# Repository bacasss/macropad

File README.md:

NOTE: for latest images, scroll down. I think these old images still have some value to this haha

this is a 3x4 macropad, utilising 12 keys wired via matrix wiring with a rotary encoder and an oled display. the main microcontroller is a seeed studio xiao rp2040.

this is the first (well second time including the 1 x 3 example) creating a pcb and it was so fun learning, drawing and arranging the components and it took so long but i feel that its a vital skill that i'll definately need to touch on again

note: native files in cad folder

BOM:
1 Seeed XIAO RP2040
12x 1N4148 Diodes
12x MX-Style switches
1x EC11 Rotary encoders
1x 0.91 inch OLED display
12x white blank DSA keycaps
4x M3x16mm screws
4x M3x5mx4mm heatset inserts

Full mockup:

this is a full mockup of the entire design, including switches, the rotary encoder, the microcontroller, and the oled display

Schematic:

i ONLY found out there was a much neater way for my pcb schematic AFTER i finished it so apologies for the mess, but it was a new experience learning matrix wiring for efficient pin usage

PCB:

i tried to make the pcb as nice as possible, but this took so long haha
here it is in 3D:

final (apparently not) update, heres an image of the assembly with a translucent top plate:

andd heres the back without the cover:

UPDATE: added mounting holes to PCB and Caseee:

PCB with mouthing holes:

In 3D:

The back of the PCB in 3D:

Updated the case with holes to mount the PCB on:

Clearer view of said holes because image isnt that clear on showing it:

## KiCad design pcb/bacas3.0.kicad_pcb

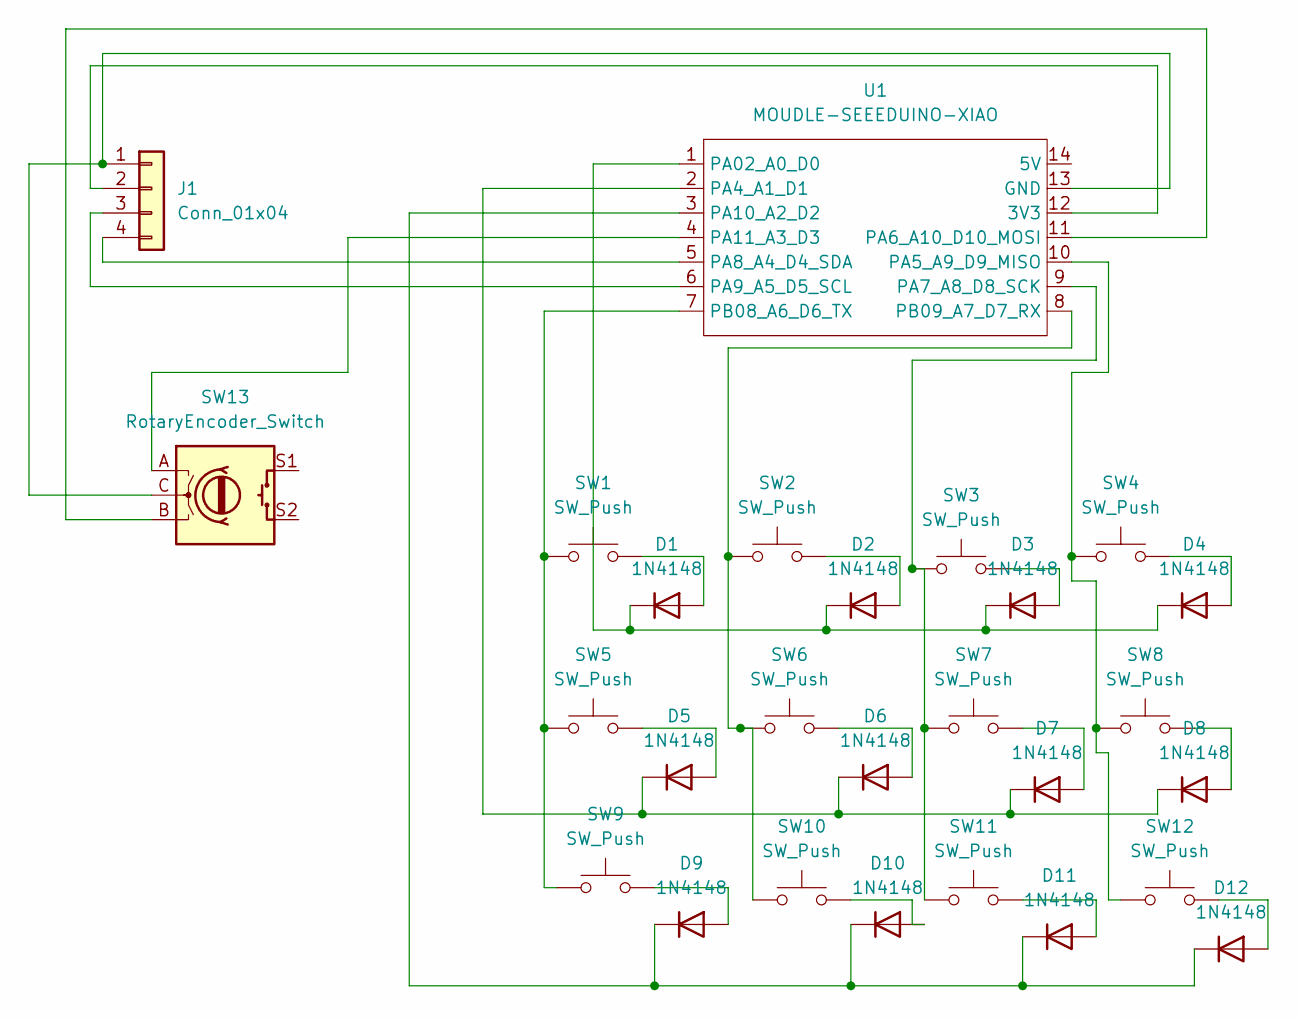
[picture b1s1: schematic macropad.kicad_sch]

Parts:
D1, D2, D3, D4, D5, D6, D7, D8, D9, D10, D11, D12: 1N4148; D_DO-35_SOD27_P7.62mm_Horizontal
J1: Conn_01x04; SSD1306-0.91-OLED-4pin-128x32 (1)
SW1, SW2, SW3, SW4, SW5, SW6, SW7, SW8, SW9, SW10, SW11, SW12: SW_Push; SW_Cherry_MX_1.00u_PCB
SW13: RotaryEncoder_Switch; RotaryEncoder_Alps_EC11E-Switch_Vertical_H20mm
U1: MOUDLE-SEEEDUINO-XIAO; XIAO-Generic-Hybrid-14P-2.54-21X17.8MM

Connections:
unnamed: D1.2 (A), SW1.2
unnamed: D1.1 (K), D2.1 (K), D3.1 (K), D4.1 (K), U1.1 (PA02_A0_D0)
unnamed: D2.2 (A), SW2.2
unnamed: D3.2 (A), SW3.2
unnamed: D4.2 (A), SW4.2
unnamed: D5.2 (A), SW5.2
unnamed: D5.1 (K), D6.1 (K), D7.1 (K), D8.1 (K), U1.2 (PA4_A1_D1)
unnamed: D6.2 (A), SW6.2
unnamed: D7.2 (A), SW7.2
unnamed: D8.2 (A), SW8.2
unnamed: D9.2 (A), SW9.2
unnamed: D10.2 (A), SW10.2
unnamed: D9.1 (K), D10.1 (K), D11.1 (K), D12.1 (K), U1.3 (PA10_A2_D2)
unnamed: D11.2 (A), SW11.2
unnamed: D12.2 (A), SW12.2
unnamed: J1.1, SW13.C, U1.13 (GND)
unnamed: J1.2, U1.12 (3V3)
unnamed: J1.3, U1.6 (PA9_A5_D5_SCL)
unnamed: J1.4, U1.5 (PA8_A4_D4_SDA)
unnamed: SW4.1, SW8.1, SW12.1, U1.10 (PA5_A9_D9_MISO)
unnamed: SW13.B, U1.11 (PA6_A10_D10_MOSI)
unnamed: SW3.1, SW7.1, SW11.1, U1.9 (PA7_A8_D8_SCK)
unnamed: SW13.A, U1.4 (PA11_A3_D3)
unnamed: SW1.1, SW5.1, SW9.1, U1.7 (PB08_A6_D6_TX)
unnamed: SW2.1, SW6.1, SW10.1, U1.8 (PB09_A7_D7_RX)

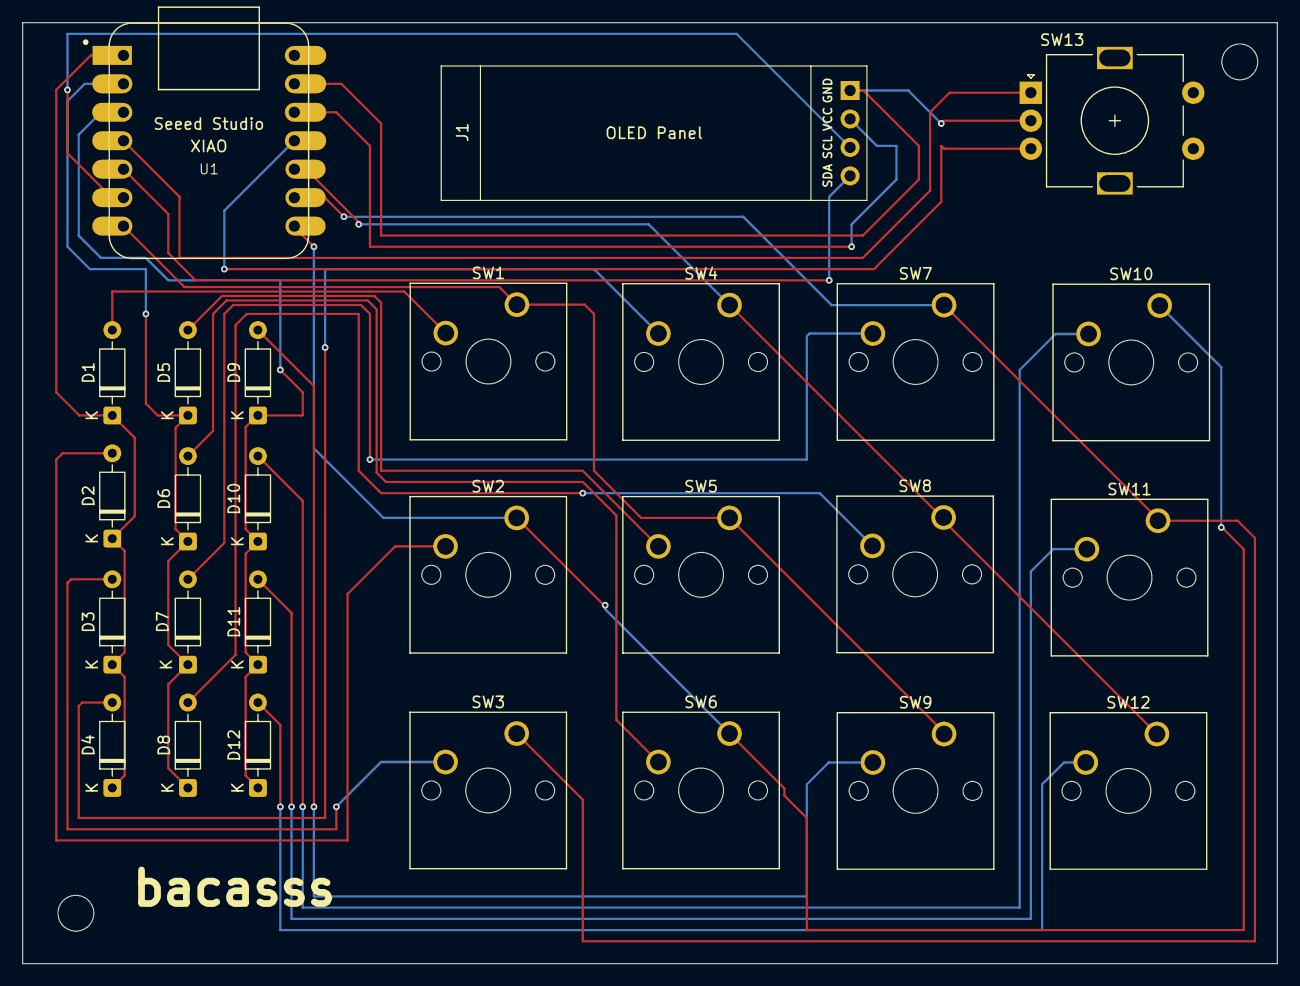
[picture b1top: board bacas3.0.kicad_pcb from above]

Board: 2 copper layers, 112.0 x 84.0 mm, 27 parts (0 on the bottom side), 25 nets.

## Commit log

2026-03-31 BOM added to README.md
2026-04-01 updated cad/macropadcase.3mf
2026-04-01 updated production/topplatestep.step
2026-04-03 updated cad/macropadcaseupdated.3mf
2026-04-03 fixed typo on code.py
2026-04-07 updated production/Casefinal.step
